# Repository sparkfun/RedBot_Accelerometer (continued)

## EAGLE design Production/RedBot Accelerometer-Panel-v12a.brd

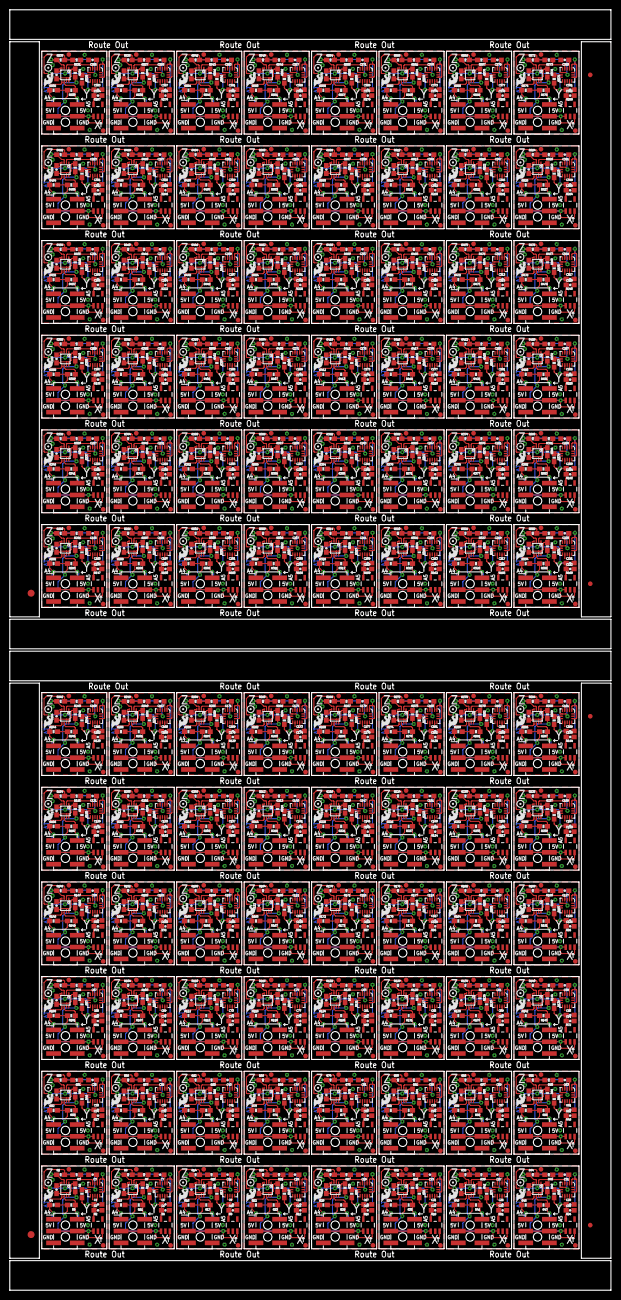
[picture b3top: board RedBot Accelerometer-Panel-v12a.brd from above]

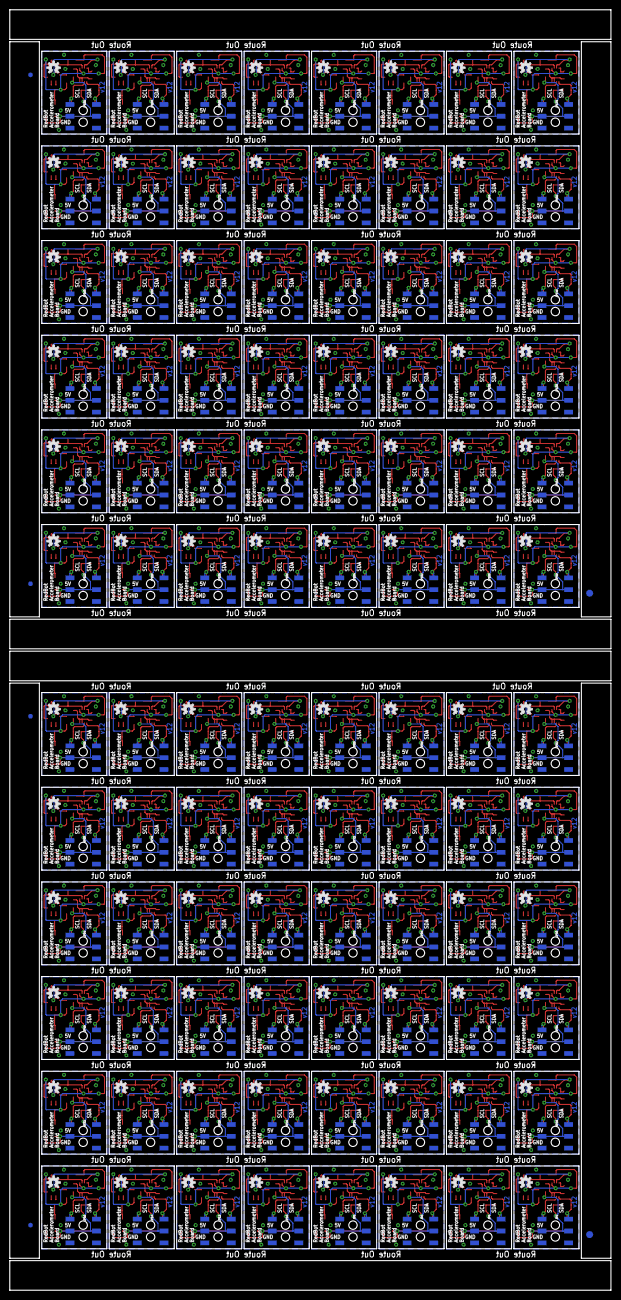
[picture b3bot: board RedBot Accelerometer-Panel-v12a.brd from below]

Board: 2 copper layers, 129.0 x 274.8 mm, 1836 parts (198 on the bottom side), 960 nets.

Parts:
C1, C3, C4, C5, C7, C8, C9, C11, C12, C13, C15, C16, C17, C19, C20, C21, C23, C24, C25, C27, C28, C29, C31, C32, C33, C35, C36, C37, C39, C40, C41, C43, C44, C45, C47, C48, C49, C51, C52, C53, C55, C56, C57, C59, C60, C61, C63, C64, C65, C67, C68, C69, C71, C72, C73, C75, C76, C77, C79, C80, C81, C83, C84, C85, C87, C88, C89, C91, C92, C93, C95, C96, C97, C99, C100, C101, C103, C104, C105, C107, C108, C109, C111, C112, C113, C115, C116, C117, C119, C120, C121, C123, C124, C125, C127, C128, C129, C131, C132, C133, C135, C136, C137, C139, C140, C141, C143, C144, C145, C147, C148, C149, C151, C152, C153, C155, C156, C157, C159, C160, C161, C163, C164, C165, C167, C168, C169, C171, C172, C173, C175, C176, C177, C179, C180, C181, C183, C184, C185, C187, C188, C189, C191, C192, C193, C195, C196, C197, C199, C200, C201, C203, C204, C205, C207, C208, C209, C211, C212, C213, C215, C216, C217, C219, C220, C221, C223, C224, C225, C227, C228, C229, C231, C232, C233, C235, C236, C237, C239, C240, C241, C243, C244, C245, C247, C248, C249, C251, C252, C253, C255, C256, C257, C259, C260, C261, C263, C264, C265, C267, C268, C269, C271, C272, C273, C275, C276, C277, C279, C280, C281, C283, C284, C285, C287, C288, C289, C291, C292, C293, C295, C296, C297, C299, C300, C301, C303, C304, C305, C307, C308, C309, C311, C312, C313, C315, C316, C317, C319, C320, C321, C323, C324, C325, C327, C328, C329, C331, C332, C333, C335, C336, C337, C339, C340, C341, C343, C344, C345, C347, C348, C349, C351, C352, C353, C355, C356, C357, C359, C360, C361, C363, C364, C365, C367, C368, C369, C371, C372, C373, C375, C376, C377, C379, C380, C381, C383, C384: 0.1uF; 0603-CAP
C2, C6, C10, C14, C18, C22, C26, C30, C34, C38, C42, C46, C50, C54, C58, C62, C66, C70, C74, C78, C82, C86, C90, C94, C98, C102, C106, C110, C114, C118, C122, C126, C130, C134, C138, C142, C146, C150, C154, C158, C162, C166, C170, C174, C178, C182, C186, C190, C194, C198, C202, C206, C210, C214, C218, C222, C226, C230, C234, C238, C242, C246, C250, C254, C258, C262, C266, C270, C274, C278, C282, C286, C290, C294, C298, C302, C306, C310, C314, C318, C322, C326, C330, C334, C338, C342, C346, C350, C354, C358, C362, C366, C370, C374, C378, C382: 4.7uF; 0603-CAP
E$1, E$6, E$7, E$11: FIDUCIAL-1.5X3
E$2, E$3, E$4, E$5, E$8, E$9, E$10, E$12: FIDUCIAL-1X2
FID1, FID2, FID3, FID4, FID5, FID6, FID7, FID8, FID9, FID10, FID11, FID12, FID13, FID14, FID15, FID16, FID17, FID18, FID19, FID20, FID21, FID22, FID23, FID24, FID25, FID26, FID27, FID28, FID29, FID30, FID31, FID32, FID33, FID34, FID35, FID36, FID37, FID38, FID39, FID40, FID41, FID42, FID43, FID44, FID45, FID46, FID47, FID48, FID49, FID50, FID51, FID52, FID53, FID54, FID55, FID56, FID57, FID58, FID59, FID60, FID61, FID62, FID63, FID64, FID65, FID66, FID67, FID68, FID69, FID70, FID71, FID72, FID73, FID74, FID75, FID76, FID77, FID78, FID79, FID80, FID81, FID82, FID83, FID84, FID85, FID86, FID87, FID88, FID89, FID90, FID91, FID92, FID93, FID94, FID95, FID96, FID97, FID98, FID99, FID100, FID101, FID102, FID103, FID104, FID105, FID106, FID107, FID108, FID109, FID110, FID111, FID112, FID113, FID114, FID115, FID116, FID117, FID118, FID119, FID120, FID121, FID122, FID123, FID124, FID125, FID126, FID127, FID128, FID129, FID130, FID131, FID132, FID133, FID134, FID135, FID136, FID137, FID138, FID139, FID140, FID141, FID142, FID143, FID144, FID145, FID146, FID147, FID148, FID149, FID150, FID151, FID152, FID153, FID154, FID155, FID156, FID157, FID158, FID159, FID160, FID161, FID162, FID163, FID164, FID165, FID166, FID167, FID168, FID169, FID170, FID171, FID172, FID173, FID174, FID175, FID176, FID177, FID178, FID179, FID180, FID181, FID182, FID183, FID184, FID185, FID186, FID187, FID188, FID189, FID190, FID191, FID192: FIDUCIAL1X2; FIDUCIAL-1X2
JP1, JP3, JP5, JP7, JP9, JP11, JP13, JP15, JP17, JP19, JP21, JP23, JP25, JP27, JP29, JP31, JP33, JP35, JP37, JP39, JP41, JP43, JP45, JP47, JP49, JP51, JP53, JP55, JP57, JP59, JP61, JP63, JP65, JP67, JP69, JP71, JP73, JP75, JP77, JP79, JP81, JP83, JP85, JP87, JP89, JP91, JP93, JP95, JP97, JP99, JP101, JP103, JP105, JP107, JP109, JP111, JP113, JP115, JP117, JP119, JP121, JP123, JP125, JP127, JP129, JP131, JP133, JP135, JP137, JP139, JP141, JP143, JP145, JP147, JP149, JP151, JP153, JP155, JP157, JP159, JP161, JP163, JP165, JP167, JP169, JP171, JP173, JP175, JP177, JP179, JP181, JP183, JP185, JP187, JP189, JP191: 2X3_SMT_POSTS
JP2, JP4, JP6, JP8, JP10, JP12, JP14, JP16, JP18, JP20, JP22, JP24, JP26, JP28, JP30, JP32, JP34, JP36, JP38, JP40, JP42, JP44, JP46, JP48, JP50, JP52, JP54, JP56, JP58, JP60, JP62, JP64, JP66, JP68, JP70, JP72, JP74, JP76, JP78, JP80, JP82, JP84, JP86, JP88, JP90, JP92, JP94, JP96, JP98, JP100, JP102, JP104, JP106, JP108, JP110, JP112, JP114, JP116, JP118, JP120, JP122, JP124, JP126, JP128, JP130, JP132, JP134, JP136, JP138, JP140, JP142, JP144, JP146, JP148, JP150, JP152, JP154, JP156, JP158, JP160, JP162, JP164, JP166, JP168, JP170, JP172, JP174, JP176, JP178, JP180, JP182, JP184, JP186, JP188, JP190, JP192: 2X3_SMD
LOGO1, LOGO3, LOGO5, LOGO7, LOGO9, LOGO11, LOGO13, LOGO15, LOGO17, LOGO19, LOGO21, LOGO23, LOGO25, LOGO27, LOGO29, LOGO31, LOGO33, LOGO35, LOGO37, LOGO39, LOGO41, LOGO43, LOGO45, LOGO47, LOGO49, LOGO51, LOGO53, LOGO55, LOGO57, LOGO59, LOGO61, LOGO63, LOGO65, LOGO67, LOGO69, LOGO71, LOGO73, LOGO75, LOGO77, LOGO79, LOGO81, LOGO83, LOGO85, LOGO87, LOGO89, LOGO91, LOGO93, LOGO95, LOGO97, LOGO99, LOGO101, LOGO103, LOGO105, LOGO107, LOGO109, LOGO111, LOGO113, LOGO115, LOGO117, LOGO119, LOGO121, LOGO123, LOGO125, LOGO127, LOGO129, LOGO131, LOGO133, LOGO135, LOGO137, LOGO139, LOGO141, LOGO143, LOGO145, LOGO147, LOGO149, LOGO151, LOGO153, LOGO155, LOGO157, LOGO159, LOGO161, LOGO163, LOGO165, LOGO167, LOGO169, LOGO171, LOGO173, LOGO175, LOGO177, LOGO179, LOGO181, LOGO183, LOGO185, LOGO187, LOGO189, LOGO191: LOGO-SFESK; SFE-LOGO-FLAME
LOGO2, LOGO4, LOGO6, LOGO8, LOGO10, LOGO12, LOGO14, LOGO16, LOGO18, LOGO20, LOGO22, LOGO24, LOGO26, LOGO28, LOGO30, LOGO32, LOGO34, LOGO36, LOGO38, LOGO40, LOGO42, LOGO44, LOGO46, LOGO48, LOGO50, LOGO52, LOGO54, LOGO56, LOGO58, LOGO60, LOGO62, LOGO64, LOGO66, LOGO68, LOGO70, LOGO72, LOGO74, LOGO76, LOGO78, LOGO80, LOGO82, LOGO84, LOGO86, LOGO88, LOGO90, LOGO92, LOGO94, LOGO96, LOGO98, LOGO100, LOGO102, LOGO104, LOGO106, LOGO108, LOGO110, LOGO112, LOGO114, LOGO116, LOGO118, LOGO120, LOGO122, LOGO124, LOGO126, LOGO128, LOGO130, LOGO132, LOGO134, LOGO136, LOGO138, LOGO140, LOGO142, LOGO144, LOGO146, LOGO148, LOGO150, LOGO152, LOGO154, LOGO156, LOGO158, LOGO160, LOGO162, LOGO164, LOGO166, LOGO168, LOGO170, LOGO172, LOGO174, LOGO176, LOGO178, LOGO180, LOGO182, LOGO184, LOGO186, LOGO188, LOGO190, LOGO192: OSHW-LOGOS; OSHW-LOGO-S
R1, R7, R13, R19, R25, R31, R37, R43, R49, R55, R61, R67, R73, R79, R85, R91, R97, R103, R109, R115, R121, R127, R133, R139, R145, R151, R157, R163, R169, R175, R181, R187, R193, R199, R205, R211, R217, R223, R229, R235, R241, R247, R253, R259, R265, R271, R277, R283, R289, R295, R301, R307, R313, R319, R325, R331, R337, R343, R349, R355, R361, R367, R373, R379, R385, R391, R397, R403, R409, R415, R421, R427, R433, R439, R445, R451, R457, R463, R469, R475, R481, R487, R493, R499, R505, R511, R517, R523, R529, R535, R541, R547, R553, R559, R565, R571: 10k; 0603-RES
R2, R3, R4, R5, R8, R9, R10, R11, R14, R15, R16, R17, R20, R21, R22, R23, R26, R27, R28, R29, R32, R33, R34, R35, R38, R39, R40, R41, R44, R45, R46, R47, R50, R51, R52, R53, R56, R57, R58, R59, R62, R63, R64, R65, R68, R69, R70, R71, R74, R75, R76, R77, R80, R81, R82, R83, R86, R87, R88, R89, R92, R93, R94, R95, R98, R99, R100, R101, R104, R105, R106, R107, R110, R111, R112, R113, R116, R117, R118, R119, R122, R123, R124, R125, R128, R129, R130, R131, R134, R135, R136, R137, R140, R141, R142, R143, R146, R147, R148, R149, R152, R153, R154, R155, R158, R159, R160, R161, R164, R165, R166, R167, R170, R171, R172, R173, R176, R177, R178, R179, R182, R183, R184, R185, R188, R189, R190, R191, R194, R195, R196, R197, R200, R201, R202, R203, R206, R207, R208, R209, R212, R213, R214, R215, R218, R219, R220, R221, R224, R225, R226, R227, R230, R231, R232, R233, R236, R237, R238, R239, R242, R243, R244, R245, R248, R249, R250, R251, R254, R255, R256, R257, R260, R261, R262, R263, R266, R267, R268, R269, R272, R273, R274, R275, R278, R279, R280, R281, R284, R285, R286, R287, R290, R291, R292, R293, R296, R297, R298, R299, R302, R303, R304, R305, R308, R309, R310, R311, R314, R315, R316, R317, R320, R321, R322, R323, R326, R327, R328, R329, R332, R333, R334, R335, R338, R339, R340, R341, R344, R345, R346, R347, R350, R351, R352, R353, R356, R357, R358, R359, R362, R363, R364, R365, R368, R369, R370, R371, R374, R375, R376, R377, R380, R381, R382, R383, R386, R387, R388, R389, R392, R393, R394, R395, R398, R399, R400, R401, R404, R405, R406, R407, R410, R411, R412, R413, R416, R417, R418, R419, R422, R423, R424, R425, R428, R429, R430, R431, R434, R435, R436, R437, R440, R441, R442, R443, R446, R447, R448, R449, R452, R453, R454, R455, R458, R459, R460, R461, R464, R465, R466, R467, R470, R471, R472, R473, R476, R477, R478, R479, R482, R483, R484, R485, R488, R489, R490, R491, R494, R495, R496, R497, R500, R501, R502, R503, R506, R507, R508, R509, R512, R513, R514, R515, R518, R519, R520, R521, R524, R525, R526, R527, R530, R531, R532, R533, R536, R537, R538, R539, R542, R543, R544, R545, R548, R549, R550, R551, R554, R555, R556, R557, R560, R561, R562, R563, R566, R567, R568, R569, R572, R573, R574, R575: 1k; 0603-RES
R6, R12, R18, R24, R30, R36, R42, R48, R54, R60, R66, R72, R78, R84, R90, R96, R102, R108, R114, R120, R126, R132, R138, R144, R150, R156, R162, R168, R174, R180, R186, R192, R198, R204, R210, R216, R222, R228, R234, R240, R246, R252, R258, R264, R270, R276, R282, R288, R294, R300, R306, R312, R318, R324, R330, R336, R342, R348, R354, R360, R366, R372, R378, R384, R390, R396, R402, R408, R414, R420, R426, R432, R438, R444, R450, R456, R462, R468, R474, R480, R486, R492, R498, R504, R510, R516, R522, R528, R534, R540, R546, R552, R558, R564, R570, R576: 200k; 0603-RES
U1, U5, U8, U11, U14, U17, U20, U23, U26, U29, U32, U35, U38, U41, U44, U47, U50, U53, U56, U59, U62, U65, U68, U71, U74, U77, U80, U83, U86, U89, U92, U95, U98, U101, U104, U107, U110, U113, U116, U119, U122, U125, U128, U131, U134, U137, U140, U143, U146, U149, U152, U155, U158, U161, U164, U167, U170, U173, U176, U179, U182, U185, U188, U191, U194, U197, U200, U203, U206, U209, U212, U215, U218, U221, U224, U227, U230, U233, U236, U239, U242, U245, U248, U251, U254, U257, U260, U263, U266, U269, U272, U275, U278, U281, U284, U287: MMA8452QMMA8452Q-1:1; MMA8452Q-1:1
U2, U6, U9, U12, U15, U18, U21, U24, U27, U30, U33, U36, U39, U42, U45, U48, U51, U54, U57, U60, U63, U66, U69, U72, U75, U78, U81, U84, U87, U90, U93, U96, U99, U102, U105, U108, U111, U114, U117, U120, U123, U126, U129, U132, U135, U138, U141, U144, U147, U150, U153, U156, U159, U162, U165, U168, U171, U174, U177, U180, U183, U186, U189, U192, U195, U198, U201, U204, U207, U210, U213, U216, U219, U222, U225, U228, U231, U234, U237, U240, U243, U246, U249, U252, U255, U258, U261, U264, U267, U270, U273, U276, U279, U282, U285, U288: MIC5205-3.3V; SOT23-5
U3, U4, U7, U10, U13, U16, U19, U22, U25, U28, U31, U34, U37, U40, U43, U46, U49, U52, U55, U58, U61, U64, U67, U70, U73, U76, U79, U82, U85, U88, U91, U94, U97, U100, U103, U106, U109, U112, U115, U118, U121, U124, U127, U130, U133, U136, U139, U142, U145, U148, U151, U154, U157, U160, U163, U166, U169, U172, U175, U178, U181, U184, U187, U190, U193, U196, U199, U202, U205, U208, U211, U214, U217, U220, U223, U226, U229, U232, U235, U238, U241, U244, U247, U250, U253, U256, U259, U262, U265, U268, U271, U274, U277, U280, U283, U286: PCA9306; PCA9306DC-1:1

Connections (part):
3.3V: C1.1, C2.1, R1.2, R2.2, R3.2, U1.1, U1.14, U2.5, U3.1
3.3V1: C5.1, C6.1, R7.2, R8.2, R9.2, U4.1, U5.1, U5.14, U6.5
3.3V2: C9.1, C10.1, R13.2, R14.2, R15.2, U7.1, U8.1, U8.14, U9.5
3.3V3: C13.1, C14.1, R19.2, R20.2, R21.2, U10.1, U11.1, U11.14, U12.5
3.3V4: C17.1, C18.1, R25.2, R26.2, R27.2, U13.1, U14.1, U14.14, U15.5
3.3V5: C21.1, C22.1, R31.2, R32.2, R33.2, U16.1, U17.1, U17.14, U18.5
3.3V6: C25.1, C26.1, R37.2, R38.2, R39.2, U19.1, U20.1, U20.14, U21.5
3.3V7: C29.1, C30.1, R43.2, R44.2, R45.2, U22.1, U23.1, U23.14, U24.5
3.3V8: C33.1, C34.1, R49.2, R50.2, R51.2, U25.1, U26.1, U26.14, U27.5
3.3V9: C37.1, C38.1, R55.2, R56.2, R57.2, U28.1, U29.1, U29.14, U30.5
3.3V10: C41.1, C42.1, R61.2, R62.2, R63.2, U31.1, U32.1, U32.14, U33.5
3.3V11: C45.1, C46.1, R67.2, R68.2, R69.2, U34.1, U35.1, U35.14, U36.5
3.3V12: C49.1, C50.1, R73.2, R74.2, R75.2, U37.1, U38.1, U38.14, U39.5
3.3V13: C53.1, C54.1, R79.2, R80.2, R81.2, U40.1, U41.1, U41.14, U42.5
3.3V14: C57.1, C58.1, R85.2, R86.2, R87.2, U43.1, U44.1, U44.14, U45.5
3.3V15: C61.1, C62.1, R91.2, R92.2, R93.2, U46.1, U47.1, U47.14, U48.5
3.3V16: C65.1, C66.1, R97.2, R98.2, R99.2, U49.1, U50.1, U50.14, U51.5
3.3V17: C69.1, C70.1, R103.2, R104.2, R105.2, U52.1, U53.1, U53.14, U54.5
3.3V18: C73.1, C74.1, R109.2, R110.2, R111.2, U55.1, U56.1, U56.14, U57.5
3.3V19: C77.1, C78.1, R115.2, R116.2, R117.2, U58.1, U59.1, U59.14, U60.5
3.3V20: C81.1, C82.1, R121.2, R122.2, R123.2, U61.1, U62.1, U62.14, U63.5
3.3V21: C85.1, C86.1, R127.2, R128.2, R129.2, U64.1, U65.1, U65.14, U66.5
3.3V22: C89.1, C90.1, R133.2, R134.2, R135.2, U67.1, U68.1, U68.14, U69.5
3.3V23: C93.1, C94.1, R139.2, R140.2, R141.2, U70.1, U71.1, U71.14, U72.5
3.3V24: C97.1, C98.1, R145.2, R146.2, R147.2, U73.1, U74.1, U74.14, U75.5
3.3V25: C101.1, C102.1, R151.2, R152.2, R153.2, U76.1, U77.1, U77.14, U78.5
3.3V26: C105.1, C106.1, R157.2, R158.2, R159.2, U79.1, U80.1, U80.14, U81.5
3.3V27: C109.1, C110.1, R163.2, R164.2, R165.2, U82.1, U83.1, U83.14, U84.5
3.3V28: C113.1, C114.1, R169.2, R170.2, R171.2, U85.1, U86.1, U86.14, U87.5
3.3V29: C117.1, C118.1, R175.2, R176.2, R177.2, U88.1, U89.1, U89.14, U90.5
3.3V30: C121.1, C122.1, R181.2, R182.2, R183.2, U91.1, U92.1, U92.14, U93.5
3.3V31: C125.1, C126.1, R187.2, R188.2, R189.2, U94.1, U95.1, U95.14, U96.5
3.3V32: C129.1, C130.1, R193.2, R194.2, R195.2, U97.1, U98.1, U98.14, U99.5
3.3V33: C133.1, C134.1, R199.2, R200.2, R201.2, U100.1, U101.1, U101.14, U102.5
3.3V34: C137.1, C138.1, R205.2, R206.2, R207.2, U103.1, U104.1, U104.14, U105.5
3.3V35: C141.1, C142.1, R211.2, R212.2, R213.2, U106.1, U107.1, U107.14, U108.5
3.3V36: C145.1, C146.1, R217.2, R218.2, R219.2, U109.1, U110.1, U110.14, U111.5
3.3V37: C149.1, C150.1, R223.2, R224.2, R225.2, U112.1, U113.1, U113.14, U114.5
3.3V38: C153.1, C154.1, R229.2, R230.2, R231.2, U115.1, U116.1, U116.14, U117.5
3.3V39: C157.1, C158.1, R235.2, R236.2, R237.2, U118.1, U119.1, U119.14, U120.5
3.3V40: C161.1, C162.1, R241.2, R242.2, R243.2, U121.1, U122.1, U122.14, U123.5
3.3V41: C165.1, C166.1, R247.2, R248.2, R249.2, U124.1, U125.1, U125.14, U126.5
3.3V42: C169.1, C170.1, R253.2, R254.2, R255.2, U127.1, U128.1, U128.14, U129.5
3.3V43: C173.1, C174.1, R259.2, R260.2, R261.2, U130.1, U131.1, U131.14, U132.5
3.3V44: C177.1, C178.1, R265.2, R266.2, R267.2, U133.1, U134.1, U134.14, U135.5
3.3V45: C181.1, C182.1, R271.2, R272.2, R273.2, U136.1, U137.1, U137.14, U138.5
3.3V46: C185.1, C186.1, R277.2, R278.2, R279.2, U139.1, U140.1, U140.14, U141.5
3.3V47: C189.1, C190.1, R283.2, R284.2, R285.2, U142.1, U143.1, U143.14, U144.5
3.3V48: C193.1, C194.1, R289.2, R290.2, R291.2, U145.1, U146.1, U146.14, U147.5
3.3V49: C197.1, C198.1, R295.2, R296.2, R297.2, U148.1, U149.1, U149.14, U150.5
3.3V50: C201.1, C202.1, R301.2, R302.2, R303.2, U151.1, U152.1, U152.14, U153.5
3.3V51: C205.1, C206.1, R307.2, R308.2, R309.2, U154.1, U155.1, U155.14, U156.5
3.3V52: C209.1, C210.1, R313.2, R314.2, R315.2, U157.1, U158.1, U158.14, U159.5
3.3V53: C213.1, C214.1, R319.2, R320.2, R321.2, U160.1, U161.1, U161.14, U162.5
3.3V54: C217.1, C218.1, R325.2, R326.2, R327.2, U163.1, U164.1, U164.14, U165.5
3.3V55: C221.1, C222.1, R331.2, R332.2, R333.2, U166.1, U167.1, U167.14, U168.5
3.3V56: C225.1, C226.1, R337.2, R338.2, R339.2, U169.1, U170.1, U170.14, U171.5
3.3V57: C229.1, C230.1, R343.2, R344.2, R345.2, U172.1, U173.1, U173.14, U174.5
3.3V58: C233.1, C234.1, R349.2, R350.2, R351.2, U175.1, U176.1, U176.14, U177.5
3.3V59: C237.1, C238.1, R355.2, R356.2, R357.2, U178.1, U179.1, U179.14, U180.5
3.3V60: C241.1, C242.1, R361.2, R362.2, R363.2, U181.1, U182.1, U182.14, U183.5
3.3V61: C245.1, C246.1, R367.2, R368.2, R369.2, U184.1, U185.1, U185.14, U186.5
3.3V62: C249.1, C250.1, R373.2, R374.2, R375.2, U187.1, U188.1, U188.14, U189.5
3.3V63: C253.1, C254.1, R379.2, R380.2, R381.2, U190.1, U191.1, U191.14, U192.5
3.3V64: C257.1, C258.1, R385.2, R386.2, R387.2, U193.1, U194.1, U194.14, U195.5
3.3V65: C261.1, C262.1, R391.2, R392.2, R393.2, U196.1, U197.1, U197.14, U198.5
3.3V66: C265.1, C266.1, R397.2, R398.2, R399.2, U199.1, U200.1, U200.14, U201.5
3.3V67: C269.1, C270.1, R403.2, R404.2, R405.2, U202.1, U203.1, U203.14, U204.5
3.3V68: C273.1, C274.1, R409.2, R410.2, R411.2, U205.1, U206.1, U206.14, U207.5
3.3V69: C277.1, C278.1, R415.2, R416.2, R417.2, U208.1, U209.1, U209.14, U210.5
3.3V70: C281.1, C282.1, R421.2, R422.2, R423.2, U211.1, U212.1, U212.14, U213.5
3.3V71: C285.1, C286.1, R427.2, R428.2, R429.2, U214.1, U215.1, U215.14, U216.5
3.3V72: C289.1, C290.1, R433.2, R434.2, R435.2, U217.1, U218.1, U218.14, U219.5
3.3V73: C293.1, C294.1, R439.2, R440.2, R441.2, U220.1, U221.1, U221.14, U222.5
3.3V74: C297.1, C298.1, R445.2, R446.2, R447.2, U223.1, U224.1, U224.14, U225.5
3.3V75: C301.1, C302.1, R451.2, R452.2, R453.2, U226.1, U227.1, U227.14, U228.5
3.3V76: C305.1, C306.1, R457.2, R458.2, R459.2, U229.1, U230.1, U230.14, U231.5
3.3V77: C309.1, C310.1, R463.2, R464.2, R465.2, U232.1, U233.1, U233.14, U234.5
3.3V78: C313.1, C314.1, R469.2, R470.2, R471.2, U235.1, U236.1, U236.14, U237.5
3.3V79: C317.1, C318.1, R475.2, R476.2, R477.2, U238.1, U239.1, U239.14, U240.5
3.3V80: C321.1, C322.1, R481.2, R482.2, R483.2, U241.1, U242.1, U242.14, U243.5
3.3V81: C325.1, C326.1, R487.2, R488.2, R489.2, U244.1, U245.1, U245.14, U246.5
3.3V82: C329.1, C330.1, R493.2, R494.2, R495.2, U247.1, U248.1, U248.14, U249.5
3.3V83: C333.1, C334.1, R499.2, R500.2, R501.2, U250.1, U251.1, U251.14, U252.5
3.3V84: C337.1, C338.1, R505.2, R506.2, R507.2, U253.1, U254.1, U254.14, U255.5
3.3V85: C341.1, C342.1, R511.2, R512.2, R513.2, U256.1, U257.1, U257.14, U258.5
3.3V86: C345.1, C346.1, R517.2, R518.2, R519.2, U259.1, U260.1, U260.14, U261.5
3.3V87: C349.1, C350.1, R523.2, R524.2, R525.2, U262.1, U263.1, U263.14, U264.5
3.3V88: C353.1, C354.1, R529.2, R530.2, R531.2, U265.1, U266.1, U266.14, U267.5
3.3V89: C357.1, C358.1, R535.2, R536.2, R537.2, U268.1, U269.1, U269.14, U270.5
3.3V90: C361.1, C362.1, R541.2, R542.2, R543.2, U271.1, U272.1, U272.14, U273.5
3.3V91: C365.1, C366.1, R547.2, R548.2, R549.2, U274.1, U275.1, U275.14, U276.5
3.3V92: C369.1, C370.1, R553.2, R554.2, R555.2, U277.1, U278.1, U278.14, U279.5
3.3V93: C373.1, C374.1, R559.2, R560.2, R561.2, U280.1, U281.1, U281.14, U282.5
3.3V94: C377.1, C378.1, R565.2, R566.2, R567.2, U283.1, U284.1, U284.14, U285.5
3.3V95: C381.1, C382.1, R571.2, R572.2, R573.2, U286.1, U287.1, U287.14, U288.5
5V: JP1.3, JP1.4, JP2.3, JP2.4, R4.2, R5.2, R6.2, U2.1, U2.3
5V1: JP3.3, JP3.4, JP4.3, JP4.4, R10.2, R11.2, R12.2, U6.1, U6.3
5V2: JP5.3, JP5.4, JP6.3, JP6.4, R16.2, R17.2, R18.2, U9.1, U9.3
5V3: JP7.3, JP7.4, JP8.3, JP8.4, R22.2, R23.2, R24.2, U12.1, U12.3
5V4: JP9.3, JP9.4, JP10.3, JP10.4, R28.2, R29.2, R30.2, U15.1, U15.3
5V5: JP11.3, JP11.4, JP12.3, JP12.4, R34.2, R35.2, R36.2, U18.1, U18.3
5V6: JP13.3, JP13.4, JP14.3, JP14.4, R40.2, R41.2, R42.2, U21.1, U21.3
5V7: JP15.3, JP15.4, JP16.3, JP16.4, R46.2, R47.2, R48.2, U24.1, U24.3
5V8: JP17.3, JP17.4, JP18.3, JP18.4, R52.2, R53.2, R54.2, U27.1, U27.3
5V9: JP19.3, JP19.4, JP20.3, JP20.4, R58.2, R59.2, R60.2, U30.1, U30.3
5V10: JP21.3, JP21.4, JP22.3, JP22.4, R64.2, R65.2, R66.2, U33.1, U33.3
5V11: JP23.3, JP23.4, JP24.3, JP24.4, R70.2, R71.2, R72.2, U36.1, U36.3
5V12: JP25.3, JP25.4, JP26.3, JP26.4, R76.2, R77.2, R78.2, U39.1, U39.3
5V13: JP27.3, JP27.4, JP28.3, JP28.4, R82.2, R83.2, R84.2, U42.1, U42.3
5V14: JP29.3, JP29.4, JP30.3, JP30.4, R88.2, R89.2, R90.2, U45.1, U45.3
5V15: JP31.3, JP31.4, JP32.3, JP32.4, R94.2, R95.2, R96.2, U48.1, U48.3
5V16: JP33.3, JP33.4, JP34.3, JP34.4, R100.2, R101.2, R102.2, U51.1, U51.3
5V17: JP35.3, JP35.4, JP36.3, JP36.4, R106.2, R107.2, R108.2, U54.1, U54.3
5V18: JP37.3, JP37.4, JP38.3, JP38.4, R112.2, R113.2, R114.2, U57.1, U57.3
5V19: JP39.3, JP39.4, JP40.3, JP40.4, R118.2, R119.2, R120.2, U60.1, U60.3
5V20: JP41.3, JP41.4, JP42.3, JP42.4, R124.2, R125.2, R126.2, U63.1, U63.3
5V21: JP43.3, JP43.4, JP44.3, JP44.4, R130.2, R131.2, R132.2, U66.1, U66.3
5V22: JP45.3, JP45.4, JP46.3, JP46.4, R136.2, R137.2, R138.2, U69.1, U69.3
5V23: JP47.3, JP47.4, JP48.3, JP48.4, R142.2, R143.2, R144.2, U72.1, U72.3
5V24: JP49.3, JP49.4, JP50.3, JP50.4, R148.2, R149.2, R150.2, U75.1, U75.3
5V25: JP51.3, JP51.4, JP52.3, JP52.4, R154.2, R155.2, R156.2, U78.1, U78.3
5V26: JP53.3, JP53.4, JP54.3, JP54.4, R160.2, R161.2, R162.2, U81.1, U81.3
5V27: JP55.3, JP55.4, JP56.3, JP56.4, R166.2, R167.2, R168.2, U84.1, U84.3
5V28: JP57.3, JP57.4, JP58.3, JP58.4, R172.2, R173.2, R174.2, U87.1, U87.3
5V29: JP59.3, JP59.4, JP60.3, JP60.4, R178.2, R179.2, R180.2, U90.1, U90.3
5V30: JP61.3, JP61.4, JP62.3, JP62.4, R184.2, R185.2, R186.2, U93.1, U93.3
5V31: JP63.3, JP63.4, JP64.3, JP64.4, R190.2, R191.2, R192.2, U96.1, U96.3
5V32: JP65.3, JP65.4, JP66.3, JP66.4, R196.2, R197.2, R198.2, U99.1, U99.3
5V33: JP67.3, JP67.4, JP68.3, JP68.4, R202.2, R203.2, R204.2, U102.1, U102.3
5V34: JP69.3, JP69.4, JP70.3, JP70.4, R208.2, R209.2, R210.2, U105.1, U105.3
5V35: JP71.3, JP71.4, JP72.3, JP72.4, R214.2, R215.2, R216.2, U108.1, U108.3
5V36: JP73.3, JP73.4, JP74.3, JP74.4, R220.2, R221.2, R222.2, U111.1, U111.3
5V37: JP75.3, JP75.4, JP76.3, JP76.4, R226.2, R227.2, R228.2, U114.1, U114.3
5V38: JP77.3, JP77.4, JP78.3, JP78.4, R232.2, R233.2, R234.2, U117.1, U117.3
5V39: JP79.3, JP79.4, JP80.3, JP80.4, R238.2, R239.2, R240.2, U120.1, U120.3
5V40: JP81.3, JP81.4, JP82.3, JP82.4, R244.2, R245.2, R246.2, U123.1, U123.3
5V41: JP83.3, JP83.4, JP84.3, JP84.4, R250.2, R251.2, R252.2, U126.1, U126.3
5V42: JP85.3, JP85.4, JP86.3, JP86.4, R256.2, R257.2, R258.2, U129.1, U129.3
5V43: JP87.3, JP87.4, JP88.3, JP88.4, R262.2, R263.2, R264.2, U132.1, U132.3
5V44: JP89.3, JP89.4, JP90.3, JP90.4, R268.2, R269.2, R270.2, U135.1, U135.3
5V45: JP91.3, JP91.4, JP92.3, JP92.4, R274.2, R275.2, R276.2, U138.1, U138.3
5V46: JP93.3, JP93.4, JP94.3, JP94.4, R280.2, R281.2, R282.2, U141.1, U141.3
5V47: JP95.3, JP95.4, JP96.3, JP96.4, R286.2, R287.2, R288.2, U144.1, U144.3
5V48: JP97.3, JP97.4, JP98.3, JP98.4, R292.2, R293.2, R294.2, U147.1, U147.3
5V49: JP99.3, JP99.4, JP100.3, JP100.4, R298.2, R299.2, R300.2, U150.1, U150.3
5V50: JP101.3, JP101.4, JP102.3, JP102.4, R304.2, R305.2, R306.2, U153.1, U153.3
5V51: JP103.3, JP103.4, JP104.3, JP104.4, R310.2, R311.2, R312.2, U156.1, U156.3
5V52: JP105.3, JP105.4, JP106.3, JP106.4, R316.2, R317.2, R318.2, U159.1, U159.3
5V53: JP107.3, JP107.4, JP108.3, JP108.4, R322.2, R323.2, R324.2, U162.1, U162.3
5V54: JP109.3, JP109.4, JP110.3, JP110.4, R328.2, R329.2, R330.2, U165.1, U165.3
5V55: JP111.3, JP111.4, JP112.3, JP112.4, R334.2, R335.2, R336.2, U168.1, U168.3
5V56: JP113.3, JP113.4, JP114.3, JP114.4, R340.2, R341.2, R342.2, U171.1, U171.3
5V57: JP115.3, JP115.4, JP116.3, JP116.4, R346.2, R347.2, R348.2, U174.1, U174.3
5V58: JP117.3, JP117.4, JP118.3, JP118.4, R352.2, R353.2, R354.2, U177.1, U177.3
5V59: JP119.3, JP119.4, JP120.3, JP120.4, R358.2, R359.2, R360.2, U180.1, U180.3
5V60: JP121.3, JP121.4, JP122.3, JP122.4, R364.2, R365.2, R366.2, U183.1, U183.3
5V61: JP123.3, JP123.4, JP124.3, JP124.4, R370.2, R371.2, R372.2, U186.1, U186.3
5V62: JP125.3, JP125.4, JP126.3, JP126.4, R376.2, R377.2, R378.2, U189.1, U189.3
5V63: JP127.3, JP127.4, JP128.3, JP128.4, R382.2, R383.2, R384.2, U192.1, U192.3
5V64: JP129.3, JP129.4, JP130.3, JP130.4, R388.2, R389.2, R390.2, U195.1, U195.3
5V65: JP131.3, JP131.4, JP132.3, JP132.4, R394.2, R395.2, R396.2, U198.1, U198.3
5V66: JP133.3, JP133.4, JP134.3, JP134.4, R400.2, R401.2, R402.2, U201.1, U201.3
5V67: JP135.3, JP135.4, JP136.3, JP136.4, R406.2, R407.2, R408.2, U204.1, U204.3
5V68: JP137.3, JP137.4, JP138.3, JP138.4, R412.2, R413.2, R414.2, U207.1, U207.3
5V69: JP139.3, JP139.4, JP140.3, JP140.4, R418.2, R419.2, R420.2, U210.1, U210.3
5V70: JP141.3, JP141.4, JP142.3, JP142.4, R424.2, R425.2, R426.2, U213.1, U213.3
5V71: JP143.3, JP143.4, JP144.3, JP144.4, R430.2, R431.2, R432.2, U216.1, U216.3
5V72: JP145.3, JP145.4, JP146.3, JP146.4, R436.2, R437.2, R438.2, U219.1, U219.3
5V73: JP147.3, JP147.4, JP148.3, JP148.4, R442.2, R443.2, R444.2, U222.1, U222.3
5V74: JP149.3, JP149.4, JP150.3, JP150.4, R448.2, R449.2, R450.2, U225.1, U225.3
5V75: JP151.3, JP151.4, JP152.3, JP152.4, R454.2, R455.2, R456.2, U228.1, U228.3
5V76: JP153.3, JP153.4, JP154.3, JP154.4, R460.2, R461.2, R462.2, U231.1, U231.3
5V77: JP155.3, JP155.4, JP156.3, JP156.4, R466.2, R467.2, R468.2, U234.1, U234.3
5V78: JP157.3, JP157.4, JP158.3, JP158.4, R472.2, R473.2, R474.2, U237.1, U237.3
5V79: JP159.3, JP159.4, JP160.3, JP160.4, R478.2, R479.2, R480.2, U240.1, U240.3
5V80: JP161.3, JP161.4, JP162.3, JP162.4, R484.2, R485.2, R486.2, U243.1, U243.3
5V81: JP163.3, JP163.4, JP164.3, JP164.4, R490.2, R491.2, R492.2, U246.1, U246.3
5V82: JP165.3, JP165.4, JP166.3, JP166.4, R496.2, R497.2, R498.2, U249.1, U249.3
5V83: JP167.3, JP167.4, JP168.3, JP168.4, R502.2, R503.2, R504.2, U252.1, U252.3
5V84: JP169.3, JP169.4, JP170.3, JP170.4, R508.2, R509.2, R510.2, U255.1, U255.3
5V85: JP171.3, JP171.4, JP172.3, JP172.4, R514.2, R515.2, R516.2, U258.1, U258.3
5V86: JP173.3, JP173.4, JP174.3, JP174.4, R520.2, R521.2, R522.2, U261.1, U261.3
5V87: JP175.3, JP175.4, JP176.3, JP176.4, R526.2, R527.2, R528.2, U264.1, U264.3
5V88: JP177.3, JP177.4, JP178.3, JP178.4, R532.2, R533.2, R534.2, U267.1, U267.3
5V89: JP179.3, JP179.4, JP180.3, JP180.4, R538.2, R539.2, R540.2, U270.1, U270.3
5V90: JP181.3, JP181.4, JP182.3, JP182.4, R544.2, R545.2, R546.2, U273.1, U273.3
5V91: JP183.3, JP183.4, JP184.3, JP184.4, R550.2, R551.2, R552.2, U276.1, U276.3
5V92: JP185.3, JP185.4, JP186.3, JP186.4, R556.2, R557.2, R558.2, U279.1, U279.3
5V93: JP187.3, JP187.4, JP188.3, JP188.4, R562.2, R563.2, R564.2, U282.1, U282.3
5V94: JP189.3, JP189.4, JP190.3, JP190.4, R568.2, R569.2, R570.2, U285.1, U285.3
5V95: JP191.3, JP191.4, JP192.3, JP192.4, R574.2, R575.2, R576.2, U288.1, U288.3
ADDR: R1.1, U1.7
ADDR1: R7.1, U5.7
ADDR2: R13.1, U8.7
ADDR3: R19.1, U11.7
ADDR4: R25.1, U14.7
ADDR5: R31.1, U17.7
ADDR6: R37.1, U20.7
ADDR7: R43.1, U23.7
ADDR8: R49.1, U26.7
ADDR9: R55.1, U29.7
ADDR10: R61.1, U32.7
ADDR11: R67.1, U35.7
ADDR12: R73.1, U38.7
ADDR13: R79.1, U41.7
ADDR14: R85.1, U44.7
ADDR15: R91.1, U47.7
ADDR16: R97.1, U50.7
ADDR17: R103.1, U53.7
ADDR18: R109.1, U56.7
ADDR19: R115.1, U59.7
ADDR20: R121.1, U62.7
ADDR21: R127.1, U65.7
ADDR22: R133.1, U68.7
ADDR23: R139.1, U71.7
ADDR24: R145.1, U74.7
ADDR25: R151.1, U77.7
ADDR26: R157.1, U80.7
ADDR27: R163.1, U83.7
ADDR28: R169.1, U86.7
ADDR29: R175.1, U89.7
ADDR30: R181.1, U92.7
ADDR31: R187.1, U95.7
ADDR32: R193.1, U98.7
ADDR33: R199.1, U101.7
ADDR34: R205.1, U104.7
ADDR35: R211.1, U107.7
ADDR36: R217.1, U110.7
ADDR37: R223.1, U113.7
ADDR38: R229.1, U116.7
ADDR39: R235.1, U119.7
ADDR40: R241.1, U122.7
ADDR41: R247.1, U125.7
ADDR42: R253.1, U128.7
ADDR43: R259.1, U131.7
ADDR44: R265.1, U134.7
ADDR45: R271.1, U137.7
ADDR46: R277.1, U140.7
ADDR47: R283.1, U143.7
ADDR48: R289.1, U146.7
ADDR49: R295.1, U149.7
ADDR50: R301.1, U152.7
ADDR51: R307.1, U155.7
ADDR52: R313.1, U158.7
ADDR53: R319.1, U161.7
ADDR54: R325.1, U164.7
ADDR55: R331.1, U167.7
ADDR56: R337.1, U170.7
ADDR57: R343.1, U173.7
ADDR58: R349.1, U176.7
ADDR59: R355.1, U179.7
ADDR60: R361.1, U182.7
ADDR61: R367.1, U185.7
ADDR62: R373.1, U188.7
ADDR63: R379.1, U191.7
ADDR64: R385.1, U194.7
ADDR65: R391.1, U197.7
ADDR66: R397.1, U200.7
ADDR67: R403.1, U203.7
ADDR68: R409.1, U206.7
ADDR69: R415.1, U209.7
ADDR70: R421.1, U212.7
ADDR71: R427.1, U215.7
ADDR72: R433.1, U218.7
ADDR73: R439.1, U221.7
ADDR74: R445.1, U224.7
ADDR75: R451.1, U227.7
ADDR76: R457.1, U230.7
ADDR77: R463.1, U233.7
ADDR78: R469.1, U236.7
ADDR79: R475.1, U239.7
ADDR80: R481.1, U242.7
ADDR81: R487.1, U245.7
ADDR82: R493.1, U248.7
ADDR83: R499.1, U251.7
ADDR84: R505.1, U254.7
ADDR85: R511.1, U257.7
ADDR86: R517.1, U260.7
ADDR87: R523.1, U263.7
ADDR88: R529.1, U266.7
ADDR89: R535.1, U269.7
ADDR90: R541.1, U272.7
ADDR91: R547.1, U275.7
ADDR92: R553.1, U278.7
ADDR93: R559.1, U281.7
ADDR94: R565.1, U284.7
ADDR95: R571.1, U287.7
GND: C1.2, C2.2, C3.2, C4.2, JP1.5, JP1.6, JP2.5, JP2.6, U1.5, U1.10, U1.12, U2.2, U3.4
GND1: C5.2, C6.2, C7.2, C8.2, JP3.5, JP3.6, JP4.5, JP4.6, U4.4, U5.5, U5.10, U5.12, U6.2
GND2: C9.2, C10.2, C11.2, C12.2, JP5.5, JP5.6, JP6.5, JP6.6, U7.4, U8.5, U8.10, U8.12, U9.2
GND3: C13.2, C14.2, C15.2, C16.2, JP7.5, JP7.6, JP8.5, JP8.6, U10.4, U11.5, U11.10, U11.12, U12.2
GND4: C17.2, C18.2, C19.2, C20.2, JP9.5, JP9.6, JP10.5, JP10.6, U13.4, U14.5, U14.10, U14.12, U15.2
GND5: C21.2, C22.2, C23.2, C24.2, JP11.5, JP11.6, JP12.5, JP12.6, U16.4, U17.5, U17.10, U17.12, U18.2
GND6: C25.2, C26.2, C27.2, C28.2, JP13.5, JP13.6, JP14.5, JP14.6, U19.4, U20.5, U20.10, U20.12, U21.2
GND7: C29.2, C30.2, C31.2, C32.2, JP15.5, JP15.6, JP16.5, JP16.6, U22.4, U23.5, U23.10, U23.12, U24.2
GND8: C33.2, C34.2, C35.2, C36.2, JP17.5, JP17.6, JP18.5, JP18.6, U25.4, U26.5, U26.10, U26.12, U27.2
GND9: C37.2, C38.2, C39.2, C40.2, JP19.5, JP19.6, JP20.5, JP20.6, U28.4, U29.5, U29.10, U29.12, U30.2
GND10: C41.2, C42.2, C43.2, C44.2, JP21.5, JP21.6, JP22.5, JP22.6, U31.4, U32.5, U32.10, U32.12, U33.2
GND11: C45.2, C46.2, C47.2, C48.2, JP23.5, JP23.6, JP24.5, JP24.6, U34.4, U35.5, U35.10, U35.12, U36.2
GND12: C49.2, C50.2, C51.2, C52.2, JP25.5, JP25.6, JP26.5, JP26.6, U37.4, U38.5, U38.10, U38.12, U39.2
GND13: C53.2, C54.2, C55.2, C56.2, JP27.5, JP27.6, JP28.5, JP28.6, U40.4, U41.5, U41.10, U41.12, U42.2
GND14: C57.2, C58.2, C59.2, C60.2, JP29.5, JP29.6, JP30.5, JP30.6, U43.4, U44.5, U44.10, U44.12, U45.2
GND15: C61.2, C62.2, C63.2, C64.2, JP31.5, JP31.6, JP32.5, JP32.6, U46.4, U47.5, U47.10, U47.12, U48.2
GND16: C65.2, C66.2, C67.2, C68.2, JP33.5, JP33.6, JP34.5, JP34.6, U49.4, U50.5, U50.10, U50.12, U51.2
GND17: C69.2, C70.2, C71.2, C72.2, JP35.5, JP35.6, JP36.5, JP36.6, U52.4, U53.5, U53.10, U53.12, U54.2
GND18: C73.2, C74.2, C75.2, C76.2, JP37.5, JP37.6, JP38.5, JP38.6, U55.4, U56.5, U56.10, U56.12, U57.2
GND19: C77.2, C78.2, C79.2, C80.2, JP39.5, JP39.6, JP40.5, JP40.6, U58.4, U59.5, U59.10, U59.12, U60.2
GND20: C81.2, C82.2, C83.2, C84.2, JP41.5, JP41.6, JP42.5, JP42.6, U61.4, U62.5, U62.10, U62.12, U63.2
GND21: C85.2, C86.2, C87.2, C88.2, JP43.5, JP43.6, JP44.5, JP44.6, U64.4, U65.5, U65.10, U65.12, U66.2
GND22: C89.2, C90.2, C91.2, C92.2, JP45.5, JP45.6, JP46.5, JP46.6, U67.4, U68.5, U68.10, U68.12, U69.2
GND23: C93.2, C94.2, C95.2, C96.2, JP47.5, JP47.6, JP48.5, JP48.6, U70.4, U71.5, U71.10, U71.12, U72.2
GND24: C97.2, C98.2, C99.2, C100.2, JP49.5, JP49.6, JP50.5, JP50.6, U73.4, U74.5, U74.10, U74.12, U75.2
GND25: C101.2, C102.2, C103.2, C104.2, JP51.5, JP51.6, JP52.5, JP52.6, U76.4, U77.5, U77.10, U77.12, U78.2
GND26: C105.2, C106.2, C107.2, C108.2, JP53.5, JP53.6, JP54.5, JP54.6, U79.4, U80.5, U80.10, U80.12, U81.2
GND27: C109.2, C110.2, C111.2, C112.2, JP55.5, JP55.6, JP56.5, JP56.6, U82.4, U83.5, U83.10, U83.12, U84.2
GND28: C113.2, C114.2, C115.2, C116.2, JP57.5, JP57.6, JP58.5, JP58.6, U85.4, U86.5, U86.10, U86.12, U87.2
GND29: C117.2, C118.2, C119.2, C120.2, JP59.5, JP59.6, JP60.5, JP60.6, U88.4, U89.5, U89.10, U89.12, U90.2
GND30: C121.2, C122.2, C123.2, C124.2, JP61.5, JP61.6, JP62.5, JP62.6, U91.4, U92.5, U92.10, U92.12, U93.2
GND31: C125.2, C126.2, C127.2, C128.2, JP63.5, JP63.6, JP64.5, JP64.6, U94.4, U95.5, U95.10, U95.12, U96.2
GND32: C129.2, C130.2, C131.2, C132.2, JP65.5, JP65.6, JP66.5, JP66.6, U97.4, U98.5, U98.10, U98.12, U99.2
GND33: C133.2, C134.2, C135.2, C136.2, JP67.5, JP67.6, JP68.5, JP68.6, U100.4, U101.5, U101.10, U101.12, U102.2
GND34: C137.2, C138.2, C139.2, C140.2, JP69.5, JP69.6, JP70.5, JP70.6, U103.4, U104.5, U104.10, U104.12, U105.2
GND35: C141.2, C142.2, C143.2, C144.2, JP71.5, JP71.6, JP72.5, JP72.6, U106.4, U107.5, U107.10, U107.12, U108.2
GND36: C145.2, C146.2, C147.2, C148.2, JP73.5, JP73.6, JP74.5, JP74.6, U109.4, U110.5, U110.10, U110.12, U111.2
GND37: C149.2, C150.2, C151.2, C152.2, JP75.5, JP75.6, JP76.5, JP76.6, U112.4, U113.5, U113.10, U113.12, U114.2
GND38: C153.2, C154.2, C155.2, C156.2, JP77.5, JP77.6, JP78.5, JP78.6, U115.4, U116.5, U116.10, U116.12, U117.2
GND39: C157.2, C158.2, C159.2, C160.2, JP79.5, JP79.6, JP80.5, JP80.6, U118.4, U119.5, U119.10, U119.12, U120.2
GND40: C161.2, C162.2, C163.2, C164.2, JP81.5, JP81.6, JP82.5, JP82.6, U121.4, U122.5, U122.10, U122.12, U123.2
GND41: C165.2, C166.2, C167.2, C168.2, JP83.5, JP83.6, JP84.5, JP84.6, U124.4, U125.5, U125.10, U125.12, U126.2
GND42: C169.2, C170.2, C171.2, C172.2, JP85.5, JP85.6, JP86.5, JP86.6, U127.4, U128.5, U128.10, U128.12, U129.2
GND43: C173.2, C174.2, C175.2, C176.2, JP87.5, JP87.6, JP88.5, JP88.6, U130.4, U131.5, U131.10, U131.12, U132.2
GND44: C177.2, C178.2, C179.2, C180.2, JP89.5, JP89.6, JP90.5, JP90.6, U133.4, U134.5, U134.10, U134.12, U135.2
GND45: C181.2, C182.2, C183.2, C184.2, JP91.5, JP91.6, JP92.5, JP92.6, U136.4, U137.5, U137.10, U137.12, U138.2
GND46: C185.2, C186.2, C187.2, C188.2, JP93.5, JP93.6, JP94.5, JP94.6, U139.4, U140.5, U140.10, U140.12, U141.2
GND47: C189.2, C190.2, C191.2, C192.2, JP95.5, JP95.6, JP96.5, JP96.6, U142.4, U143.5, U143.10, U143.12, U144.2
GND48: C193.2, C194.2, C195.2, C196.2, JP97.5, JP97.6, JP98.5, JP98.6, U145.4, U146.5, U146.10, U146.12, U147.2
GND49: C197.2, C198.2, C199.2, C200.2, JP99.5, JP99.6, JP100.5, JP100.6, U148.4, U149.5, U149.10, U149.12, U150.2
GND50: C201.2, C202.2, C203.2, C204.2, JP101.5, JP101.6, JP102.5, JP102.6, U151.4, U152.5, U152.10, U152.12, U153.2
GND51: C205.2, C206.2, C207.2, C208.2, JP103.5, JP103.6, JP104.5, JP104.6, U154.4, U155.5, U155.10, U155.12, U156.2
GND52: C209.2, C210.2, C211.2, C212.2, JP105.5, JP105.6, JP106.5, JP106.6, U157.4, U158.5, U158.10, U158.12, U159.2
GND53: C213.2, C214.2, C215.2, C216.2, JP107.5, JP107.6, JP108.5, JP108.6, U160.4, U161.5, U161.10, U161.12, U162.2
GND54: C217.2, C218.2, C219.2, C220.2, JP109.5, JP109.6, JP110.5, JP110.6, U163.4, U164.5, U164.10, U164.12, U165.2
GND55: C221.2, C222.2, C223.2, C224.2, JP111.5, JP111.6, JP112.5, JP112.6, U166.4, U167.5, U167.10, U167.12, U168.2
GND56: C225.2, C226.2, C227.2, C228.2, JP113.5, JP113.6, JP114.5, JP114.6, U169.4, U170.5, U170.10, U170.12, U171.2
GND57: C229.2, C230.2, C231.2, C232.2, JP115.5, JP115.6, JP116.5, JP116.6, U172.4, U173.5, U173.10, U173.12, U174.2
GND58: C233.2, C234.2, C235.2, C236.2, JP117.5, JP117.6, JP118.5, JP118.6, U175.4, U176.5, U176.10, U176.12, U177.2
GND59: C237.2, C238.2, C239.2, C240.2, JP119.5, JP119.6, JP120.5, JP120.6, U178.4, U179.5, U179.10, U179.12, U180.2
GND60: C241.2, C242.2, C243.2, C244.2, JP121.5, JP121.6, JP122.5, JP122.6, U181.4, U182.5, U182.10, U182.12, U183.2
GND61: C245.2, C246.2, C247.2, C248.2, JP123.5, JP123.6, JP124.5, JP124.6, U184.4, U185.5, U185.10, U185.12, U186.2
GND62: C249.2, C250.2, C251.2, C252.2, JP125.5, JP125.6, JP126.5, JP126.6, U187.4, U188.5, U188.10, U188.12, U189.2
GND63: C253.2, C254.2, C255.2, C256.2, JP127.5, JP127.6, JP128.5, JP128.6, U190.4, U191.5, U191.10, U191.12, U192.2
GND64: C257.2, C258.2, C259.2, C260.2, JP129.5, JP129.6, JP130.5, JP130.6, U193.4, U194.5, U194.10, U194.12, U195.2
GND65: C261.2, C262.2, C263.2, C264.2, JP131.5, JP131.6, JP132.5, JP132.6, U196.4, U197.5, U197.10, U197.12, U198.2
GND66: C265.2, C266.2, C267.2, C268.2, JP133.5, JP133.6, JP134.5, JP134.6, U199.4, U200.5, U200.10, U200.12, U201.2
GND67: C269.2, C270.2, C271.2, C272.2, JP135.5, JP135.6, JP136.5, JP136.6, U202.4, U203.5, U203.10, U203.12, U204.2
GND68: C273.2, C274.2, C275.2, C276.2, JP137.5, JP137.6, JP138.5, JP138.6, U205.4, U206.5, U206.10, U206.12, U207.2
GND69: C277.2, C278.2, C279.2, C280.2, JP139.5, JP139.6, JP140.5, JP140.6, U208.4, U209.5, U209.10, U209.12, U210.2
GND70: C281.2, C282.2, C283.2, C284.2, JP141.5, JP141.6, JP142.5, JP142.6, U211.4, U212.5, U212.10, U212.12, U213.2
GND71: C285.2, C286.2, C287.2, C288.2, JP143.5, JP143.6, JP144.5, JP144.6, U214.4, U215.5, U215.10, U215.12, U216.2
GND72: C289.2, C290.2, C291.2, C292.2, JP145.5, JP145.6, JP146.5, JP146.6, U217.4, U218.5, U218.10, U218.12, U219.2
GND73: C293.2, C294.2, C295.2, C296.2, JP147.5, JP147.6, JP148.5, JP148.6, U220.4, U221.5, U221.10, U221.12, U222.2
GND74: C297.2, C298.2, C299.2, C300.2, JP149.5, JP149.6, JP150.5, JP150.6, U223.4, U224.5, U224.10, U224.12, U225.2
GND75: C301.2, C302.2, C303.2, C304.2, JP151.5, JP151.6, JP152.5, JP152.6, U226.4, U227.5, U227.10, U227.12, U228.2
GND76: C305.2, C306.2, C307.2, C308.2, JP153.5, JP153.6, JP154.5, JP154.6, U229.4, U230.5, U230.10, U230.12, U231.2
GND77: C309.2, C310.2, C311.2, C312.2, JP155.5, JP155.6, JP156.5, JP156.6, U232.4, U233.5, U233.10, U233.12, U234.2
GND78: C313.2, C314.2, C315.2, C316.2, JP157.5, JP157.6, JP158.5, JP158.6, U235.4, U236.5, U236.10, U236.12, U237.2
GND79: C317.2, C318.2, C319.2, C320.2, JP159.5, JP159.6, JP160.5, JP160.6, U238.4, U239.5, U239.10, U239.12, U240.2
GND80: C321.2, C322.2, C323.2, C324.2, JP161.5, JP161.6, JP162.5, JP162.6, U241.4, U242.5, U242.10, U242.12, U243.2
GND81: C325.2, C326.2, C327.2, C328.2, JP163.5, JP163.6, JP164.5, JP164.6, U244.4, U245.5, U245.10, U245.12, U246.2
GND82: C329.2, C330.2, C331.2, C332.2, JP165.5, JP165.6, JP166.5, JP166.6, U247.4, U248.5, U248.10, U248.12, U249.2
GND83: C333.2, C334.2, C335.2, C336.2, JP167.5, JP167.6, JP168.5, JP168.6, U250.4, U251.5, U251.10, U251.12, U252.2
GND84: C337.2, C338.2, C339.2, C340.2, JP169.5, JP169.6, JP170.5, JP170.6, U253.4, U254.5, U254.10, U254.12, U255.2
GND85: C341.2, C342.2, C343.2, C344.2, JP171.5, JP171.6, JP172.5, JP172.6, U256.4, U257.5, U257.10, U257.12, U258.2
GND86: C345.2, C346.2, C347.2, C348.2, JP173.5, JP173.6, JP174.5, JP174.6, U259.4, U260.5, U260.10, U260.12, U261.2
GND87: C349.2, C350.2, C351.2, C352.2, JP175.5, JP175.6, JP176.5, JP176.6, U262.4, U263.5, U263.10, U263.12, U264.2
GND88: C353.2, C354.2, C355.2, C356.2, JP177.5, JP177.6, JP178.5, JP178.6, U265.4, U266.5, U266.10, U266.12, U267.2
GND89: C357.2, C358.2, C359.2, C360.2, JP179.5, JP179.6, JP180.5, JP180.6, U268.4, U269.5, U269.10, U269.12, U270.2
GND90: C361.2, C362.2, C363.2, C364.2, JP181.5, JP181.6, JP182.5, JP182.6, U271.4, U272.5, U272.10, U272.12, U273.2
GND91: C365.2, C366.2, C367.2, C368.2, JP183.5, JP183.6, JP184.5, JP184.6, U274.4, U275.5, U275.10, U275.12, U276.2
GND92: C369.2, C370.2, C371.2, C372.2, JP185.5, JP185.6, JP186.5, JP186.6, U277.4, U278.5, U278.10, U278.12, U279.2
GND93: C373.2, C374.2, C375.2, C376.2, JP187.5, JP187.6, JP188.5, JP188.6, U280.4, U281.5, U281.10, U281.12, U282.2
GND94: C377.2, C378.2, C379.2, C380.2, JP189.5, JP189.6, JP190.5, JP190.6, U283.4, U284.5, U284.10, U284.12, U285.2
GND95: C381.2, C382.2, C383.2, C384.2, JP191.5, JP191.6, JP192.5, JP192.6, U286.4, U287.5, U287.10, U287.12, U288.2
unnamed: C3.1, U1.2
unnamed: C4.1, R6.1, U3.7, U3.8
unnamed: C8.1, R12.1, U4.7, U4.8
unnamed: C7.1, U5.2
unnamed: C12.1, R18.1, U7.7, U7.8
unnamed: C11.1, U8.2
unnamed: C16.1, R24.1, U10.7, U10.8
unnamed: C15.1, U11.2
unnamed: C20.1, R30.1, U13.7, U13.8
unnamed: C19.1, U14.2
unnamed: C24.1, R36.1, U16.7, U16.8
unnamed: C23.1, U17.2
unnamed: C28.1, R42.1, U19.7, U19.8
unnamed: C27.1, U20.2
unnamed: C32.1, R48.1, U22.7, U22.8
unnamed: C31.1, U23.2
unnamed: C36.1, R54.1, U25.7, U25.8
unnamed: C35.1, U26.2
unnamed: C40.1, R60.1, U28.7, U28.8
unnamed: C39.1, U29.2
unnamed: C44.1, R66.1, U31.7, U31.8
unnamed: C43.1, U32.2
unnamed: C48.1, R72.1, U34.7, U34.8
unnamed: C47.1, U35.2
unnamed: C52.1, R78.1, U37.7, U37.8
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
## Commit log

2013-03-08 v01 files for protos.
2013-03-08 Add some part info for BOM purposes.
2013-05-15 Advance to rev 10 for release - added pin numbers for alignment to top silk - change revision numbers
2013-05-17 Production readied
    added fiducial references & created panel for manufacture
2013-10-22 Rev for v11 protos
2013-11-26 added fiducials to board
2013-11-26 created panel
2014-05-15 Added 1:1 for PCA and Accel , 0603 update
2014-06-19 added regular fiducial to board, deleted old panel
2014-06-19 created panel v12
2014-08-13 Deleting v10 panel from production files
2014-08-13 Fixing board files
2014-09-09 Fixing version numbers
2015-01-07 changed fids from micro to regular
2015-01-07 created panel v12a
    this panel allows for better depanelization of the boards
2015-09-08 created large v12a panel
2015-09-21 added bottom side panel fiducials
2020-05-27 pushing v14
2020-05-27 updating old packages
2020-05-27 post-review changes
2020-05-29 panelizing
2021-04-15 Update Readme
    Adding updated photo for v14 release.
